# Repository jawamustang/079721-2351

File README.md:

# 079721-2351
Mazda Mx-5 Na 1990 board
 Mazda MX-5 Miata Ecu reverse engineered
 
 Ecu version B63H
 079700-2633
 18 881c
 
 PCB version 079721-2351

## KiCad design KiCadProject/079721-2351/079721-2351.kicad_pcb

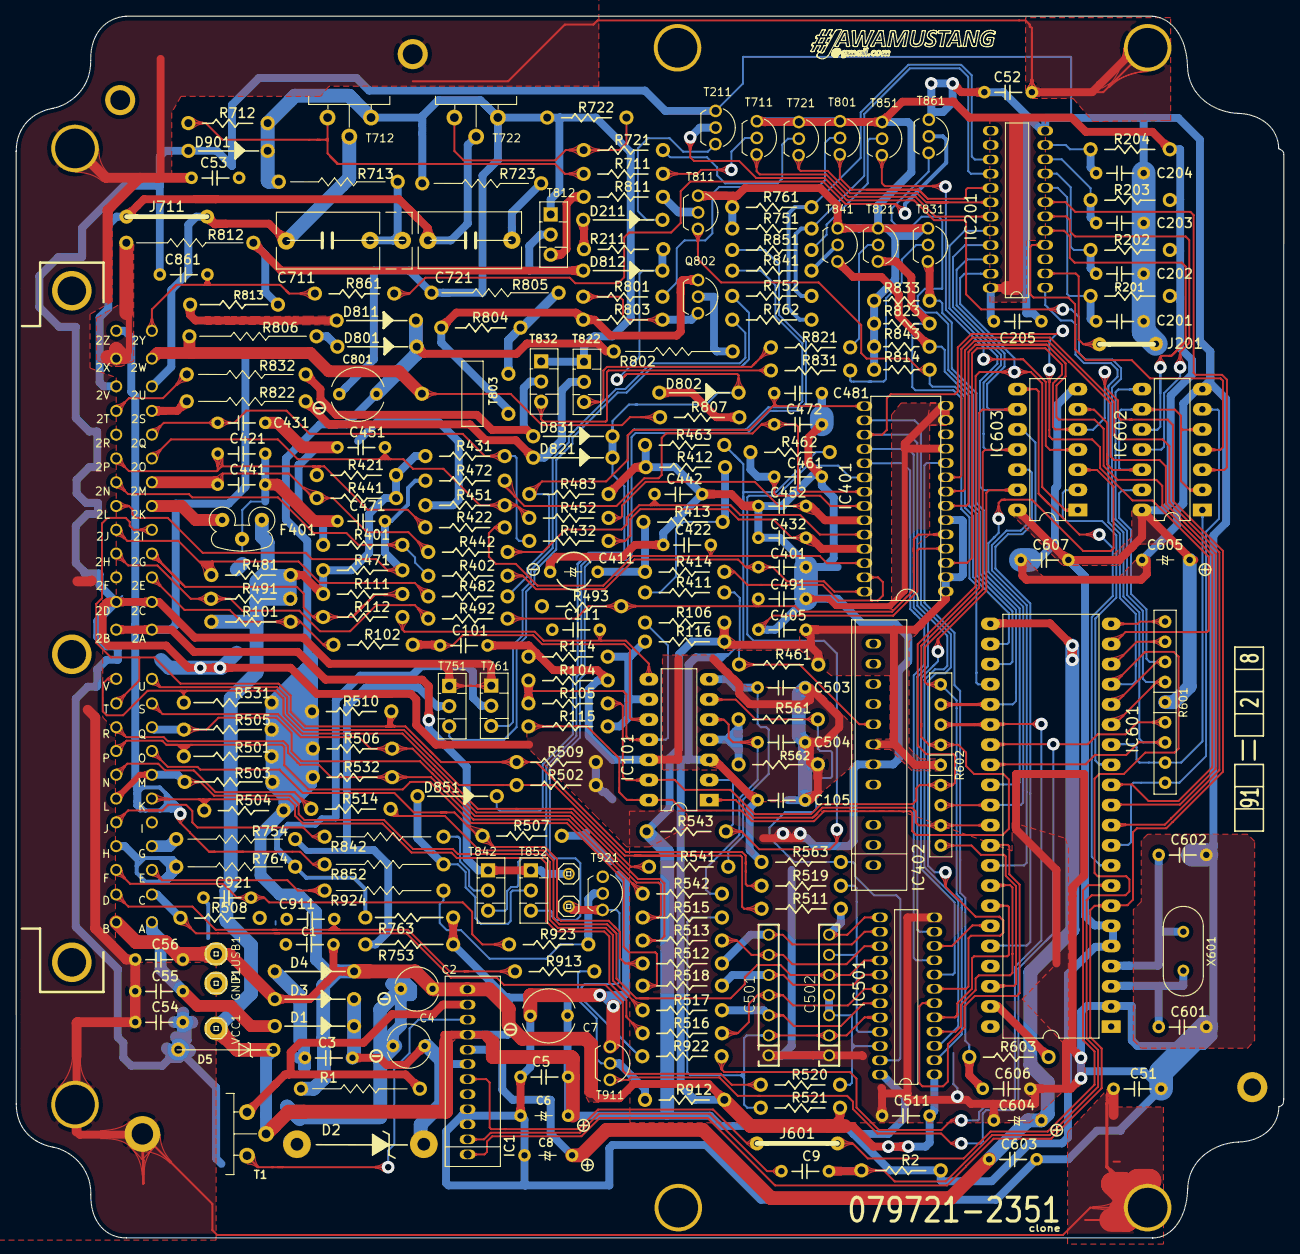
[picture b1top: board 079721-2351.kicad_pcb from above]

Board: 2 copper layers, 159.9 x 154.1 mm, 241 parts (0 on the bottom side), 180 nets.

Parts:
C1, C3, C105, C421, C431, C451, C471, C503, C504, C511, C911, C921: 47nf; C_6mm
C2, C4: 33uf35Velec; C_electrolytic_6mm_P4mm
C5, C9, C52, C53, C54, C55, C56, C401, C405, C422, C432, C442, C461, C472, C481, C491, C603, C607: 10nF (103); C_6mm
C6, C8, C604, C605: 3.3uF 16V; C_tantalum_6mm
C7: 220uf10Velec; C_electrolytic_7mm_P5mm
C51, C441, C861: empty; C_6mm
C101, C204: 1nF (102) 100V; C_6mm
C111: 10nF50V; C_6mm
C201, C202, C203: 3,3nF (332) 100V; C_6mm
C205, C452: 100nf; C_6mm
C411: 3.3uf50Velec; capacitorPolarisedMazda6mm
C501, C502: C_Array_7; C_array_6
C601, C602, C606: 20 pF (20); C_6mm
C711: 680fF 100V; C_rect_17mm_7m_3_pin
C721: 680fF 100V; C_rect_13mm_7m_2_pin
C801: 47uf35Velec; C_electrolytic_7mm_P5mm
D1, D3, D4, D801, D802, D811, D812, D901: 1E1; D
D2: about 27v 5W; D_zener_big
D5: 6.2B1; D_zener_small
D211: Not sure propably zener; D
D821, D831, D851: empty; D
F401: 223s; EMI_filter_LCL
GND1: Conn_01x01_Female; pinhead-1-1X01
H1: MountingHole; MountingHole_2.7mm_M2.5_ISO7380_Pad
H2, H3, H4: MountingHole_Pad; MountingHole_5mm
H6, H10: MountingHole; MountingHole_2.2mm_M2_ISO14580_Pad
H7: MountingHole_Pad; MountingHole_2.2mm_M2_ISO14580_Pad
H8, H9, H11: MountingHole; MountingHole_5mm
IC1: HC244
IC101: uPC177C; DIP-14_W7.62mm_LongPads
IC201: MP493; DIL24S
IC401: D151811-0360; DIL28S
IC402: IS157
IC501: D151821-0020; DIL24S
IC601: MP5273
IC602: 4071; DIP-14_W7.62mm_LongPads
IC603: 4069; DIP-14_W7.62mm_LongPads
J44: Conn_02x11_0x13_Top_Bottom_Shielded-MazdaProjekt_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; Connector_13x02_11x02_174917-6
J201: Connected; J_short
J601: Connected; J
J711: Empty; J
PLUSB1: Conn_01x01_Female; pinhead-1-1X01
Q802: C945; TO-92
R1, R822, R832, R852, R924: empty; R_15mm
R2, R102, R112, R211, R402, R422, R441, R442, R462, R463, R472, R481, R482, R511, R512, R513, R514, R515, R516, R517, R518, R519, R520, R541, R542, R561: 10k; R_10mm
R101, R712: 1K; R_10mm
R104, R114, R521: 22k; R_10mm
R105, R115: 13k; R_10mm
R106, R116, R563: 18k; R_10mm
R111, R414, R722: 1k; R_10mm
R201, R203: 68K 2%; R_10mm
R202: 100K 2%; R_10mm
R204: 36K 2%; R_10mm
R401: 1.5M; R_10mm
R411, R412: 1k 2%; R_10mm
R413: 36K; R_10mm
R421, R431: 2,7K2%; R_10mm
R432, R452, R493: 10K; R_10mm
R451, R461, R483, R491, R492, R509, R821, R831, R851, R861: empty; R_10mm
R471, R543, R803, R807, R912: 4.7k; R_10mm
R501, R503, R505, R531: 680R; R_12mm
R502, R504, R506, R507, R508, R510, R532, R751, R761, R801, R804: 2.2k; R_10mm
R562: 30K; R_10mm
R601: R_Network08_US_mazda; R_arrray_8
R602: R; R_arrray_8
R603, R711, R721, R752, R762, R811, R841, R922: 300R; R_10mm
R713, R723: 47R 1W; R_15mm
R753, R763, R813: 63R; R_12mm
R754, R764: 2.2R (m 2.8R) 1W; R_15mm
R802: 361R 1W; R_15mm
R805, R806: 8.2R2W; R_17mm
R812: 3.9R2W; R_17mm
R814, R843: empty; R_7mm
R823, R833: 4.7K; R_7mm
R842: 3.9R (m 4.8R) 1W; R_15mm
R913, R923: 330R; R_10mm
T1: 2SB1015B
T211, T911, T921: RN1006; TO-92
T711, T721, T801, T841: 2CS2001; TO-92
T712, T722: 2SD1415
T751, T761, T812, T842: CE1A3Q; TO-126-3_Vertical
T803: 2CS4065; 2SC4065
T811: 2SC1815; TO-92
T821, T831, T851, T861: Empty; TO-92
T822, T832, T852: CE1A3Q (empty); TO-126-3_Vertical
T921A1, T921B1: Conn_01x01_Female; pinhead-1-1X01
VCC1: Conn_01x01_Female; pinhead-1-1X01
X601: Crystal; Crystal_HC18-U_Vertical

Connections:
2S: J44.2S, R822.2
2T: J44.2T, R832.2
2Y: C861.1, J44.2Y, R861.2
+5V: C5.1, C6.1, C7.1, C205.2, C405.1, C605.1, C607.1, D5.1, F401.3, IC1.4, IC201.24, IC401.1, IC401.2, IC401.6, IC402.6, IC501.24, IC601.4, IC601.5, IC602.14, IC603.14, R2.1, R101.2, R106.1, R111.2, R116.1, R201.1, R202.1, R203.1, R204.1, R421.1, R431.2, R441.1, R461.1, R471.2, R481.1, R491.1, R543.2, R601.5, R602.5, R751.2, R753.1, R761.2, R763.1, R814.2, R823.2, R833.2, R843.2, T1.1, T711.1, T721.1, T801.1, T811.1, T821.1, T831.1, T841.1, T851.1, VCC1.1
+12V: C1.1, C2.1, C56.1, C105.2, C511.1, C801.1, D3.2, D4.1, D801.1, D811.1, IC1.1, IC101.3, IC501.1, J44.B, PLUSB1.1, R1.2, R411.1, R501.1, R503.1, R504.1, R505.1, R506.2, R510.2, R521.1, R531.1, R532.2, R563.2, R802.2, R912.1
+BATT: C55.1, D1.2, J44.A
/IC201_8: C201.2, IC201.8, R201.2
/IC201_9: C202.2, IC201.9, R202.2
/IC201_10: C203.2, IC201.10, R203.2
/IC201_11: C204.2, IC201.11, R204.2
/IC201_15: IC201.15, R761.1, R762.1
/IC201_16: IC201.16, R751.1, R752.1
/IC201_17: IC201.17, T801.3
/IC201_18: IC201.18, T721.3
/IC201_19: IC201.19, T711.3
/IC401_5: C491.2, IC401.5, R492.1, R493.1
/IC401_15: C481.2, IC401.15, R482.1, R483.2
/IC401_20: IC101.2, IC401.20, R543.1
/IC401_21: C472.2, IC401.21, R472.1
/IC401_22: C461.2, IC401.22, R462.2
/IC401_23: C452.1, IC401.23, R452.1
/IC401_24: C442.2, IC401.24, R442.1
/IC401_25: C432.1, IC401.25, R432.1
/IC401_26: C422.1, IC401.26, R422.1
/IC401_27: IC401.27, R414.1
/IC401_28: C401.2, IC401.28, R402.1
/IC501_13: C502.7, IC501.13, R511.1
/IC501_14: C501.7, IC501.14, R512.1
/IC501_15: C501.6, IC501.15, R513.1
/IC501_16: C502.5, IC501.16, R514.1
/IC501_17: C501.5, IC501.17, R518.1
/IC501_18: C501.4, IC501.18, R516.1
/IC501_19: C501.3, IC501.19, R517.1
/IC501_20: C501.2, C502.2, IC501.20, R515.1, R521.2
/IC501_21: C502.6, IC501.21, R519.1
/IC501_22: C502.3, C502.4, IC501.22, R520.1
/IC601_7: IC601.7, J601.2
/IC601_8: IC601.8, IC603.8
/IC601_13: IC601.13, IC603.2
/IC601_21: C8.1, C603.2, C604.1, IC1.5, IC601.21
/IC601_22: IC601.22, R814.1, T811.3
/IC601_23: IC601.23, R843.1, T841.3
/IC601_24: IC601.24, R823.1, T821.3
/IC601_29: IC601.29, R833.1, T831.3
/IC601_33: IC601.33, IC603.12
/IC601_37: IC601.37, IC603.10
/IC601_40: IC601.40, R603.1
AC_relay: J44.J, R842.2
AC_switch: J44.Q, R505.2, R515.2
Airflow_meter_5V: F401.1, J44.2K
Airflow_meter_intake_air_thermosensor: C421.2, J44.2P, R421.2, R422.2
Blower_motor_switch: J44.S, R506.1, R513.2
California_emission: J44.2H, R491.2, R492.2
Check_engine_indicator: J44.E, R924.2
Crank_angle_sensor_G_CMP: J44.2G, R111.1, R112.2
Crank_angle_sensor_N_CPK: J44.2E, R101.1, R102.2
D851: D802.1, D812.1, D821.1, D831.1, D851.1, R211.1
EVAP_canister_purage_valve: J44.2X, R812.2
GND: C801.2, D901.1, J44.2A, J44.2B, R712.1, R713.2, R722.2, R723.2, R805.2, T712.3, T722.3, T812.1, T822.1, T832.1, T842.1, T852.1, T921A1.1
GNDA: C51.2, C52.1, C53.2, C54.2, C55.2, C56.2, H1.1, H2.1, H3.1, H4.1, H7.1, H11.1
GNDS: C1.2, C2.2, C3.2, C4.2, C5.2, C6.2, C7.2, C8.2, C51.1, C52.2, C53.1, C54.1, C101.1, C105.1, C111.2, C201.1, C202.1, C203.1, C204.1, C205.1, C401.1, C405.2, C411.2, C421.1, C422.2, C431.1, C432.2, C441.1, C442.1, C451.2, C452.2, C461.1, C471.2, C472.1, C481.1, C491.1, C501.1, C502.1, C503.1, C504.1, C511.2, C601.1, C602.1, C603.1, C604.2, C605.2, C606.1, C607.2, C861.2, C911.2, C921.2, D2.2, D4.2, D5.2, D901.2, F401.2, GND1.1, IC1.9, IC1.10, IC101.12, IC201.12, IC401.4, IC401.11, IC401.13, IC401.14, IC402.5, IC501.12, IC601.1, IC602.7, IC603.7, J44.2C, J44.2D, J201.2, R104.1, R114.2, R401.2, R412.2, R451.2, R463.2, R483.1, R493.2, R502.1, R507.1, R508.1, R509.1, R562.1, T211.1, T751.1, T761.1, T861.1, T911.1, T921.1
Headlight_switch: J44.U, R502.2, R511.2
IC201_4: IC201.4, IC602.4
IC201_5: IC201.5, IC602.10
IC201_6: IC201.6, IC602.11
IC201_7: IC201.7, IC602.3
IC201_20: IC201.20, IC501.8, IC603.13
IC201_21: IC201.21, IC501.2, IC603.11, R602.9
IC201_22: IC101.14, IC201.22, IC603.9, R115.2, R602.6
IC201_23: IC101.13, IC201.23, IC603.1, R105.1, R602.4
IC401_10: C606.2, IC401.10, R603.2
IC401_16: IC401.16, IC501.7
IC401_18: IC401.18, IC501.11
IC401_19: IC401.19, IC501.9
IC601_6: IC1.12, IC401.3, IC601.6, IC603.5
IC601_9: IC601.9, IC602.6, R601.1
IC601_10: IC401.9, IC601.10
IC601_11: IC401.8, IC601.11
IC601_12: IC401.7, IC601.12
IC601_14: IC601.14, IC602.1, R601.2
IC601_15: IC601.15, IC602.8, R601.6
IC601_16: IC601.16, IC602.13, R601.7
IC601_17: C9.1, IC201.1, IC601.17, R2.2
IC601_18: IC601.18, R601.8
IC601_19: IC401.17, IC501.3, IC601.19
IC601_20: IC601.20, R601.9
IC601_25: IC601.25, R602.8, T861.3
IC601_26: IC601.26, R602.7, R922.1
IC601_27: IC601.27, R601.4, T911.3
IC601_28: IC601.28, R601.3, T211.2
IC601_30: IC601.30, IC603.3, R602.3
IC601_31: IC101.1, IC601.31, R602.2
IC601_32: IC501.6, IC601.32
IC601_34: IC501.4, IC601.34
IC601_35: IC501.5, IC601.35
IC601_36: IC501.10, IC601.36
IC601_39: IC601.39, R602.1
Idle_air_control_valve: J44.2W, R806.2, R807.2, T803.2
Igniter_E: J44.2I, J44.T, R509.2, R510.1, R519.2
Ignition_amp_1&4: J44.G, R754.2
Ignition_amp_2&3: J44.H, R764.2
Injectors_1_3: C711.1, J44.2U, J711.2, T712.2
Injectors_2_4: C721.2, J44.2V, J711.1, T722.2
K: J44.K, R504.2, R516.2
unnamed: C3.1, C4.1, D1.1, D2.1, D3.1, IC1.6
unnamed: C9.2, IC1.11
unnamed: C101.2, IC101.10, R102.1
unnamed: C111.1, IC101.8, R112.1
unnamed: C411.1, R413.2, R414.2
unnamed: C503.2, IC101.7, R541.1
unnamed: C504.2, IC101.5, R542.1
unnamed: C601.2, IC601.2, X601.2
unnamed: C602.2, IC601.3, X601.1
unnamed: C711.2, R713.1
unnamed: C721.1, R723.1
unnamed: D211.1, T211.3
unnamed: D211.2, R211.2
unnamed: D801.2, R806.1
unnamed: D802.2, R807.1
unnamed: D811.2, R813.2
unnamed: D812.2, R812.1, R813.1, T812.2
unnamed: D821.2, R822.1, T822.2
unnamed: D831.2, R832.1, T832.2
unnamed: D851.2, R852.1, T852.2
unnamed: IC1.2, R1.1, T1.3
unnamed: IC1.3, T1.2
unnamed: IC1.7, J601.1
unnamed: IC101.4, R561.2, R562.2
unnamed: IC101.9, R114.1, R115.1, R116.2
unnamed: IC101.11, R104.2, R105.2, R106.2
unnamed: IC201.2, J201.1
unnamed: IC402.7, R461.2, R462.1, R463.1
unnamed: IC602.2, IC602.5, IC602.9, IC602.12, IC603.6
unnamed: IC603.4, T851.3
unnamed: Q802.1, R803.2, R804.2, T803.3
unnamed: Q802.2, R802.1
unnamed: Q802.3, R801.2, R803.1
unnamed: R411.2, R412.1, R413.1
unnamed: R711.1, T711.2
unnamed: R711.2, R712.2, T712.1
unnamed: R721.1, T721.2
unnamed: R721.2, R722.1, T722.1
unnamed: R752.2, T751.3
unnamed: R753.2, R754.1, T751.2
unnamed: R762.2, T761.3
unnamed: R763.2, R764.1, T761.2
unnamed: R801.1, T801.2
unnamed: R804.1, R805.1, T803.1
unnamed: R811.1, T811.2
unnamed: R811.2, T812.3
unnamed: R821.1, T821.2
unnamed: R821.2, T822.3
unnamed: R831.1, T831.2
unnamed: R831.2, T832.3
unnamed: R841.1, T841.2
unnamed: R841.2, T842.3
unnamed: R842.1, T842.2
unnamed: R851.1, T851.2
unnamed: R851.2, T852.3
unnamed: R861.1, T861.2
unnamed: R912.2, R913.1, T911.2
unnamed: R922.2, T921.3, T921B1.1
unnamed: R923.1, R924.1, T921.2
Neutral_or_clutch_switch: J44.V, R531.2, R541.2
Oxygen_sensor: J44.2N, R401.1, R402.2
Power_steering_pressure_switch: J44.P, R501.2, R518.2
Radiator_fun_temperature_sensor: J44.2J, R481.2, R482.2
Radiator_temperature_switch: J44.R, R532.1, R542.2
Self_diagnostic_checker_code_no: C921.1, J44.F, R923.2
Self_diagnostic_checker_monitor_lamp: C911.1, J44.D, R913.2
Starter_motor: J44.C, R508.2, R520.2
Stoplight_switch: J44.O, R507.2, R512.2
Throttle_position_sensor: C441.2, J44.2M, R441.2, R442.2
Throttle_sensor_idle_terminal: J44.N, R514.2
Throttle_wide_open_sensor: C471.1, J44.2L, R471.1, R472.2
Transsmision_control_module: J44.2Z, R852.2
Transsmision_control_module_2: J44.L, J44.M, R503.2, R517.2
Volume_airflow_sensor: C451.1, J44.2O, R451.1, R452.2
Vref: IC101.6, IC501.23, R561.1, R563.1
Water_thermosensor: C431.2, J44.2Q, R431.1, R432.2

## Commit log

2019-10-27 Mazda Mx-5 Ecu board
2019-10-28 elements1
2019-10-30 Resistors
2019-11-01 almost all elements
2019-11-01 caps and res
2019-11-02 documentation
2019-11-02 almost all
2019-11-02 Revert "98%"
    This reverts commit 228bb048896ac542235b7dc7c177cccb8a3aded8.
2019-11-02 bugs fix
2019-11-02 res array value update
2019-11-02 all elements
2019-12-18 new_board_photo
2019-12-19 top connections
2019-12-19 nearly all lines
2019-12-19 TopReady
2019-12-25 Bottom And Top
2019-12-25 Bottom: wires -> labels
2019-12-30 top ready
2019-12-30 top2
2019-12-30 bottom
2020-01-05 complete 0.1
2020-01-05 elements
2020-01-05 Version 0.99
2020-01-05 Version 0.999
2020-01-06 Bug fix 1
2020-01-06 Bug Fix 2
2020-01-27 Pinhead to vias conversion
2020-02-09 Paths elements
2020-02-09 gnd filed zones
2020-02-10 Fixes
2020-02-12 3d model fix
2020-02-13 Board layers fix
2020-02-24 some layout fixes
2020-03-01 GND mess cleanup
2020-03-01 12V line mess cleanup
2020-03-01 Cleanup, this commit brings great chaos
2020-03-02 Schematic reordering
2020-03-02 Schematic reconfiguration
2020-03-02 cleanup
2020-03-06 Input description TODO: Correct transistors pins
2020-03-08 Schematic is Ok Libraries are messy (It needs to be fixed) Pcb shape needs to be checked Holes position are not precisely
2020-03-09 Schematic library cleanup
2020-03-09 some cleanup
2020-03-12 New footprint lib
2020-03-12 Footprints moved to local lib
2020-03-12 lib cleanup
2020-03-13 Schematic cleanup
2020-03-14 3D Models update
2020-03-15 Board shape
2020-03-18 Board cleanup
2020-03-18 Lib fix
2020-03-18 2h Pin update
2020-03-19 ic601 pinout fix
2020-03-19 IC401 pinout fix
2020-03-28 Holes locations
2020-04-05 Holes edition, masks edition
2020-04-07 Board desciption, and logo
2020-04-08 Holes correction
2020-05-17 C-array is not easy to buy, so I moved pins to fit in their place dip14 socket, so you can do your own c-array. I still need to move transistor T712, T722, T1, to perfectly fit radiators. Board holes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
2020-05-30 parts footprings update, holes positions update
2020-06-08 D151801 pins description update
